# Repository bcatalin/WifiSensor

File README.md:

### Description

A wifi sensor, designed to collect and report various sensor readings over wifi.

### Sensors

- HTU21D (Temperature + Humidity)
- MCP9808 (Temperature)
- MPL3115A2 (Pressure)
- TSL2561 (Light)
- 3x Inputs/Outputs

### Other Features

- ESP8266
- 3.3V operation
- Mini USB power connector
- Li-po charger
- Battery charging LED
- Automatic battery/USB power switching
- Solar panel input
- FTDI programming port
- Choice of 2 serial uart converters, CH340G or CP2102

### License

This work is licensed under a Creative Commons Attribution-ShareAlike 4.0 International License.

<br />
Designed by <a xmlns:cc="http://creativecommons.org/ns#" href="http://www.richardhawthorn.com" property="cc:attributionName" rel="cc:attributionURL" target="_blank">Richard Hawthorn</a><br />
<a rel="license" href="http://creativecommons.org/licenses/by-sa/4.0/" target="_blank">View License</a>

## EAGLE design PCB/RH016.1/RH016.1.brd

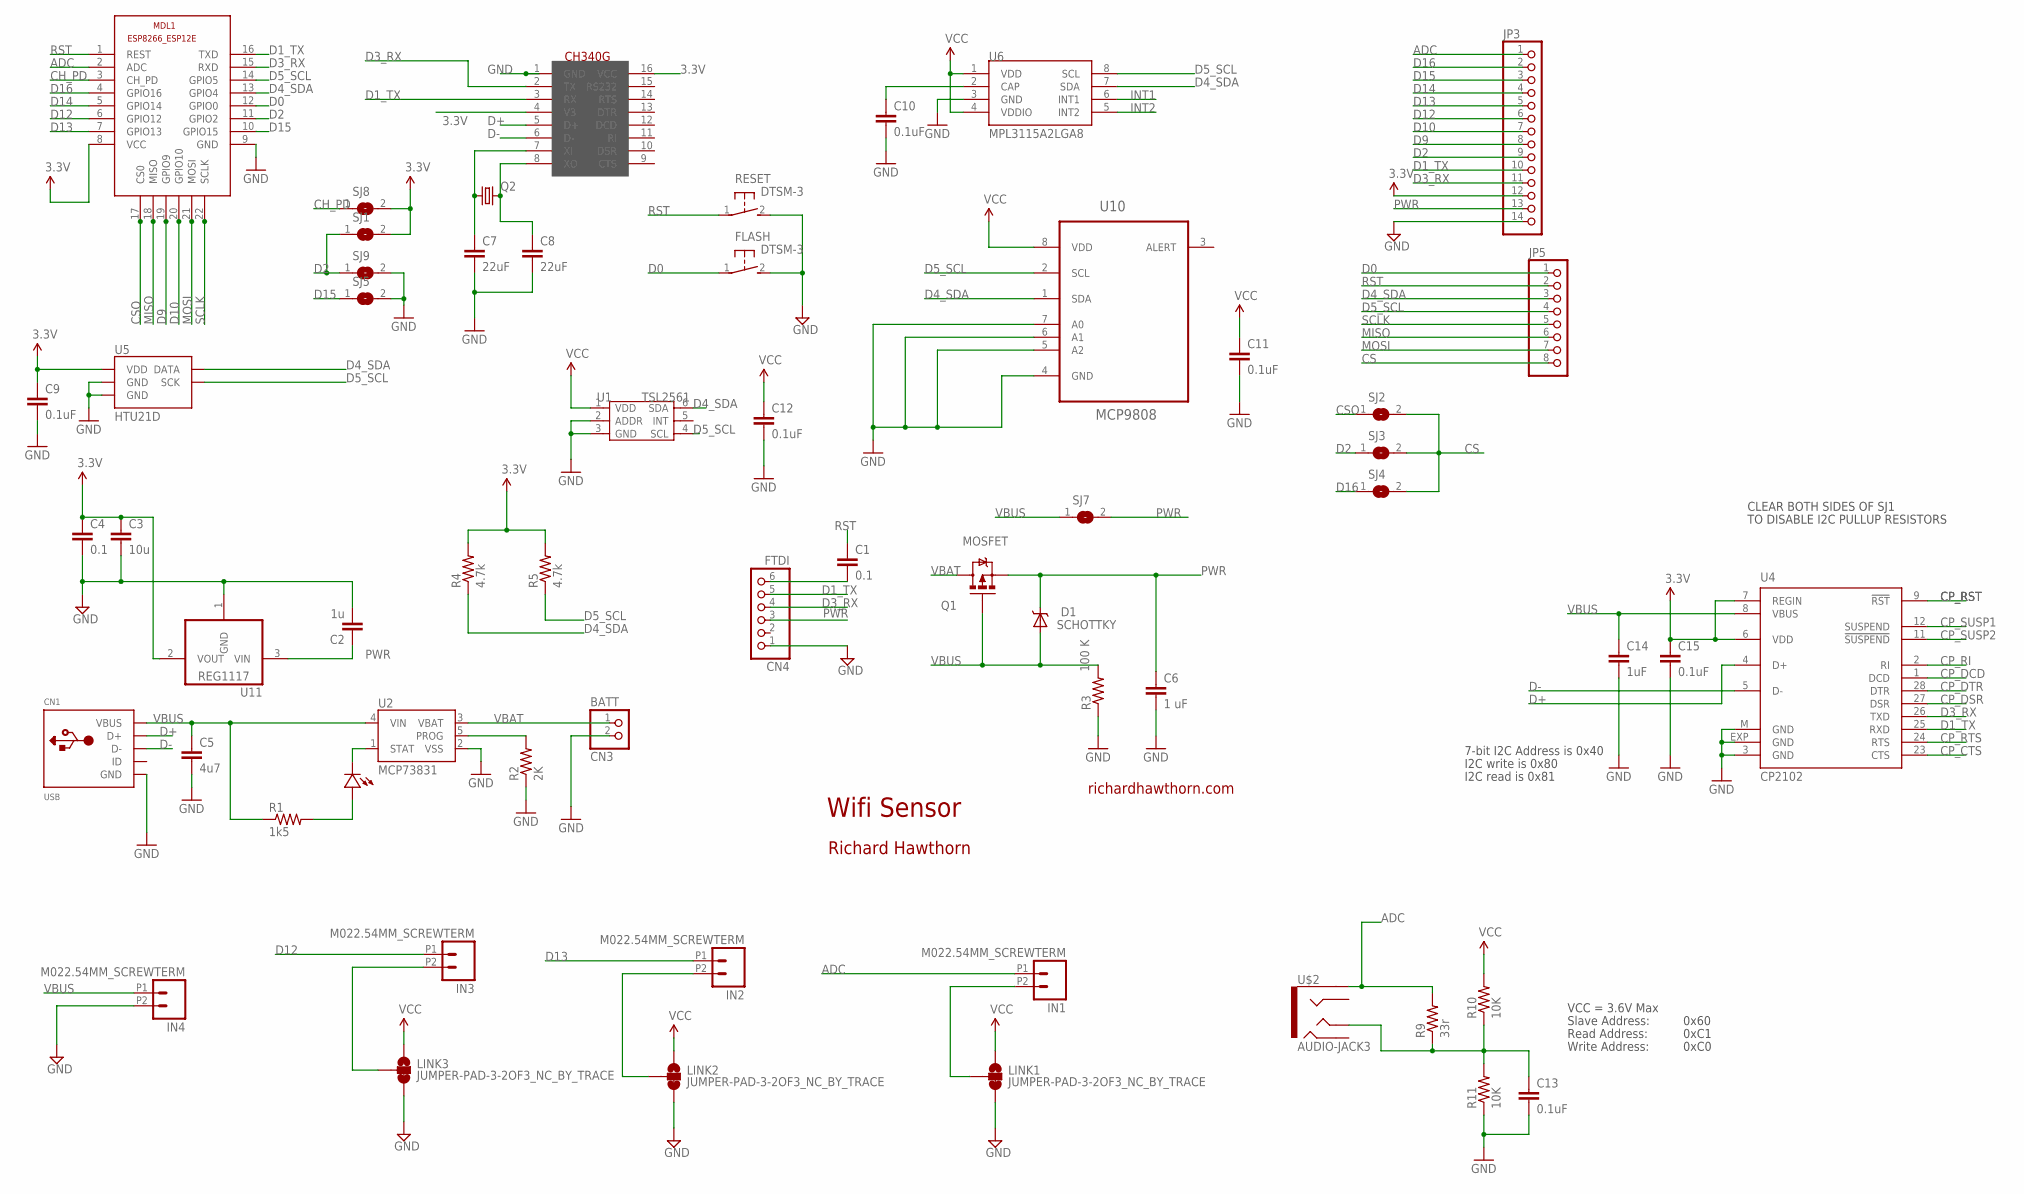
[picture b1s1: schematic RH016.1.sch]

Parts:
C1, C4: 0.1; 0603-CAP
C2: 1u; 0603-CAP
C3: 10u; 0805-CAP
C5: 4u7; 0603-CAP
C6: 1 uF; 0805
C7, C8: 22uF; 0805
C9, C10: 0.1uF; 0805
C11, C12, C13, C15: 0.1uF; 0603-CAP
C14: 1uF; 0603-CAP
CN1: USB; USB-MINIB
CN3: BATT; JST-PH-2-SMT-RA
CN4: FTDI; 1X06
D1: SCHOTTKY; SMA-DIODE
FLASH: DTSM-3
IN1, IN2, IN3, IN4: M022.54MM_SCREWTERM; 1X02_2.54_SCREWTERM
JP3: PINHD-1X14; 1X14
JP5: PINHD-1X8; 1X08
LED1: LED0603; 0603-LED
LINK1, LINK2, LINK3: JUMPER-PAD-3-2OF3_NC_BY_TRACE; PAD-JUMPER-3-2OF3_NC_BY_TRACE_YES_SILK_FULL_BOX
MDL1: ESP8266-12EESP8266-ESP12E; ESP8266-ESP12E
Q1: MOSFET; SOT23-3
Q2: CRYSTALSM49; SM49
R1: 1k5; 0603-RES
R2: 2K; 0603-RES
R3: 100 K; 0805
R4, R5: 4.7k; 0805
R9: 33r; 0603-RES
R10, R11: 10K; 0603-RES
RESET: DTSM-3
SJ1, SJ2, SJ3, SJ4, SJ5, SJ7, SJ8, SJ9: SJ
U1: TSL2561; TMB-6
U2: MCP73831; SOT23-5
U4: CP2102; MLP28
U5: HTU21D
U6: MPL3115A2LGA8; LGA8
U10: MCP9808; SOP65P490X110-8N
U11: REG1117; SOT223
U$2: AUDIO-JACK3; AUDIO-JACK-TRRS-SMD
U$4: CH340G; SOIC16

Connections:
3.3V: C3.1, C4.1, C9.1, C11.1, C12.1, C15.1, JP3.12, LINK1.1, LINK2.1, LINK3.1, MDL1.8 (VCC), R4.2, R5.2, R10.2, SJ1.2, SJ8.2, U1.1 (VDD), U4.6 (VDD), U4.7 (REGIN), U5.VDD, U6.1 (VDD), U6.4 (VDDIO), U10.8 (VDD), U11.2 (VOUT), U$4.4 (V3), U$4.16 (VCC)
ADC: IN1.P1 (1), JP3.1, MDL1.2 (ADC), R9.2, U$2.EARTH
CH_PD: MDL1.3 (CH_PD), SJ8.1
CP_CTS: U4.23 (CTS)
CP_DCD: U4.1 (DCD)
CP_DSR: U4.27 (DSR)
CP_DTR: U4.28 (DTR)
CP_RI: U4.2 (RI)
CP_RST: U4.9 (!RST)
CP_RTS: U4.24 (RTS)
CP_SUSP1: U4.12 (SUSPEND)
CP_SUSP2: U4.11 (!SUSPEND)
CS: JP5.8, SJ2.2, SJ3.2, SJ4.2
CSO: MDL1.17 (CS0), SJ2.1
D0: FLASH.1, JP5.1, MDL1.12 (GPIO0)
D1_TX: CN4.5, JP3.10, MDL1.16 (TXD), U4.25 (RXD), U$4.3 (RX)
D2: JP3.9, MDL1.11 (GPIO2), SJ1.1, SJ3.1, SJ9.1
D3_RX: CN4.4, JP3.11, MDL1.15 (RXD), U4.26 (TXD), U$4.2 (TX)
D4_SDA: JP5.3, MDL1.13 (GPIO4), R4.1, U1.6 (SDA), U5.DATA, U6.7 (SDA), U10.1 (SDA)
D5_SCL: JP5.4, MDL1.14 (GPIO5), R5.1, U1.4 (SCL), U5.SCK, U6.8 (SCL), U10.2 (SCL)
D9: JP3.8, MDL1.19 (GPIO9)
D10: JP3.7, MDL1.20 (GPIO10)
D12: IN3.P1 (1), JP3.6, MDL1.6 (GPIO12)
D13: IN2.P1 (1), JP3.5, MDL1.7 (GPIO13)
D14: JP3.4, MDL1.5 (GPIO14)
D15: JP3.3, MDL1.10 (GPIO15), SJ5.1
D16: JP3.2, MDL1.4 (GPIO16), SJ4.1
D+: CN1.D+, U4.4 (D+), U$4.5 (D+)
D-: CN1.D-, U4.5 (D-), U$4.6 (D-)
GND: C2.2, C3.2, C4.2, C5.2, C6.2, C7.2, C8.2, C9.2, C10.2, C11.2, C12.2, C13.2, C14.2, C15.2, CN1.GND, CN3.2 (1), CN4.1, FLASH.2, IN4.P2 (2), JP3.14, LINK1.3, LINK2.3, LINK3.3, MDL1.9 (GND), R2.1, R3.1, R11.1, RESET.2, SJ5.2, SJ9.2, U1.2 (ADDR), U1.3 (GND), U2.2 (VSS), U4.3 (GND), U4.EXP (GND), U4.M (GND), U5.7 (GND), U5.GND, U6.3 (GND), U10.4 (GND), U10.5 (A2), U10.6 (A1), U10.7 (A0), U11.1 (GND), U$4.1 (GND)
INT1: U6.6 (INT1)
INT2: U6.5 (INT2)
MISO: JP5.6, MDL1.18 (MISO)
MOSI: JP5.7, MDL1.21 (MOSI)
unnamed: C7.1, Q2.1, U$4.7 (XI)
unnamed: C8.1, Q2.2, U$4.8 (XO)
unnamed: LED1.PLUS, R1.2
unnamed: C10.1, U6.2 (CAP)
unnamed: IN1.P2 (2), LINK1.2
unnamed: C13.1, R9.1, R10.1, R11.2, U$2.TIP
unnamed: IN2.P2 (2), LINK2.2
unnamed: IN3.P2 (2), LINK3.2
unnamed: C1.2, CN4.6
PROG: R2.2, U2.5 (PROG)
PWR: C2.1, C6.1, CN4.3, D1.C, JP3.13, Q1.2 (S), SJ7.2, U11.3 (VIN)
RST: C1.1, JP5.2, MDL1.1 (REST), RESET.1
SCLK: JP5.5, MDL1.22 (SCLK)
STAT: LED1.MINUS, U2.1 (STAT)
VBAT: CN3.1 (2), Q1.3 (D), U2.3 (VBAT)
VBUS: C5.1, C14.1, CN1.VBUS, D1.A, IN4.P1 (1), Q1.1 (G), R1.1, R3.2, SJ7.1, U2.4 (VIN), U4.8 (VBUS)

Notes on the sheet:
Wifi Sensor
richardhawthorn.com
Richard Hawthorn
CLEAR BOTH SIDES OF SJ1
TO DISABLE I2C PULLUP RESISTORS
7-bit I2C Address is 0x40
I2C write is 0x80
I2C read is 0x81
VCC = 3.6V Max
Read Address:
Write Address:
Slave Address:
0x60
0xC1
0xC0

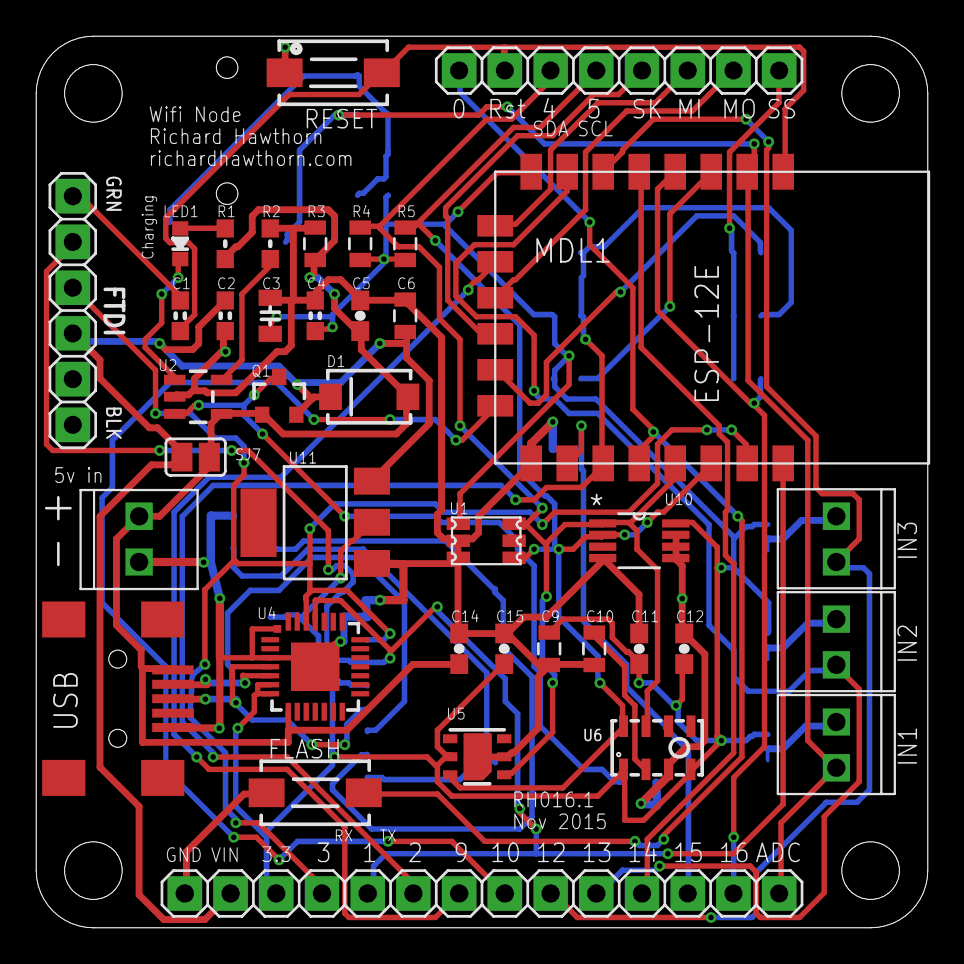
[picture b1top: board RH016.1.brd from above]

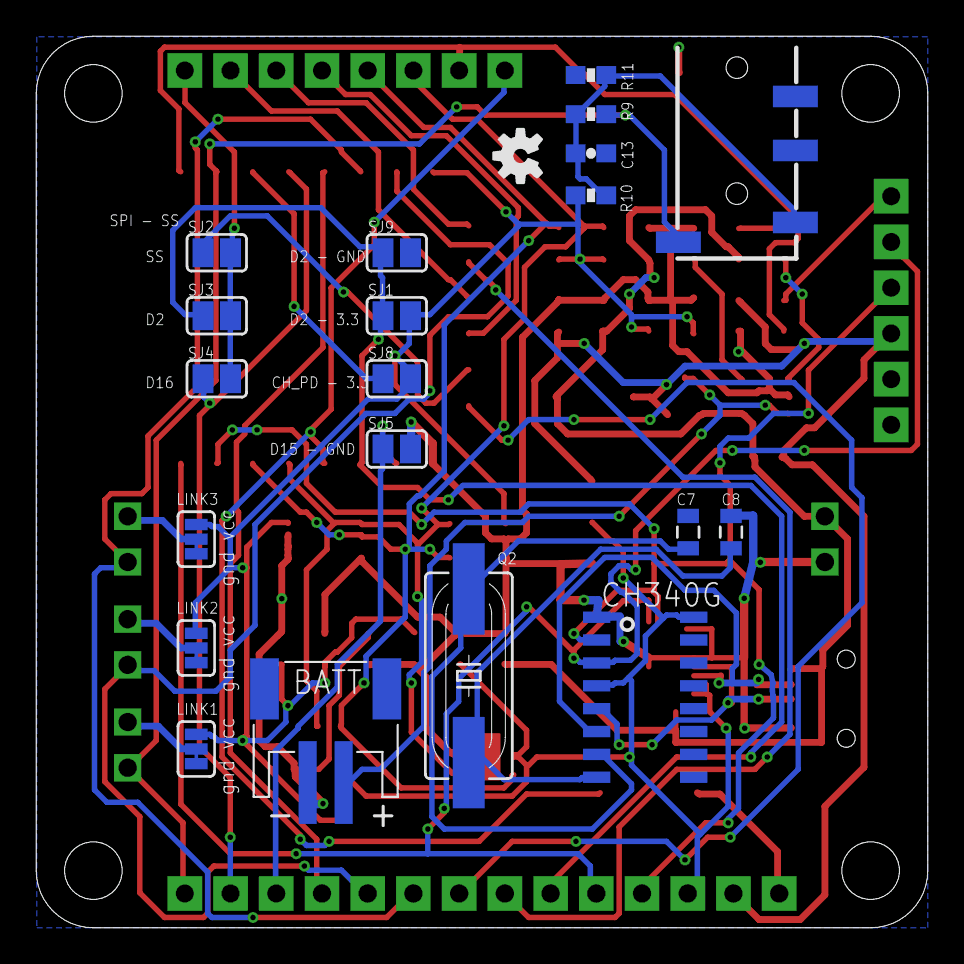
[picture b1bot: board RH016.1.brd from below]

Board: 2 copper layers, 49.5 x 49.5 mm, 60 parts (21 on the bottom side), 39 nets.

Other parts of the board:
U$3: OSHW-LOGO-S

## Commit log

2015-11-05 adding design files
2015-11-05 front pcb image
2015-11-05 updated images
2015-11-05 added gerber
2016-04-08 rename folder
2016-04-08 add images
2016-04-08 add readme

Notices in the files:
parts and their libraries:
SparkFun-Aesthetics: Licensing: CC v3.0 Share-Alike You are welcome to use this library for commercial purposes.
SparkFun-Connectors: Licensing: Creative Commons ShareAlike 4.0 International - https://creativecommons.org/licenses/by-sa/4.0
